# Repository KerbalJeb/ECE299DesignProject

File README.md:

# ECE299DesignProject

An Arduino Uno power alarm clock, complated as part of ECE299 at UVic.

The PCB desing files can be viewed online at:[CADLAB.io](https://cadlab.io/project/23071).

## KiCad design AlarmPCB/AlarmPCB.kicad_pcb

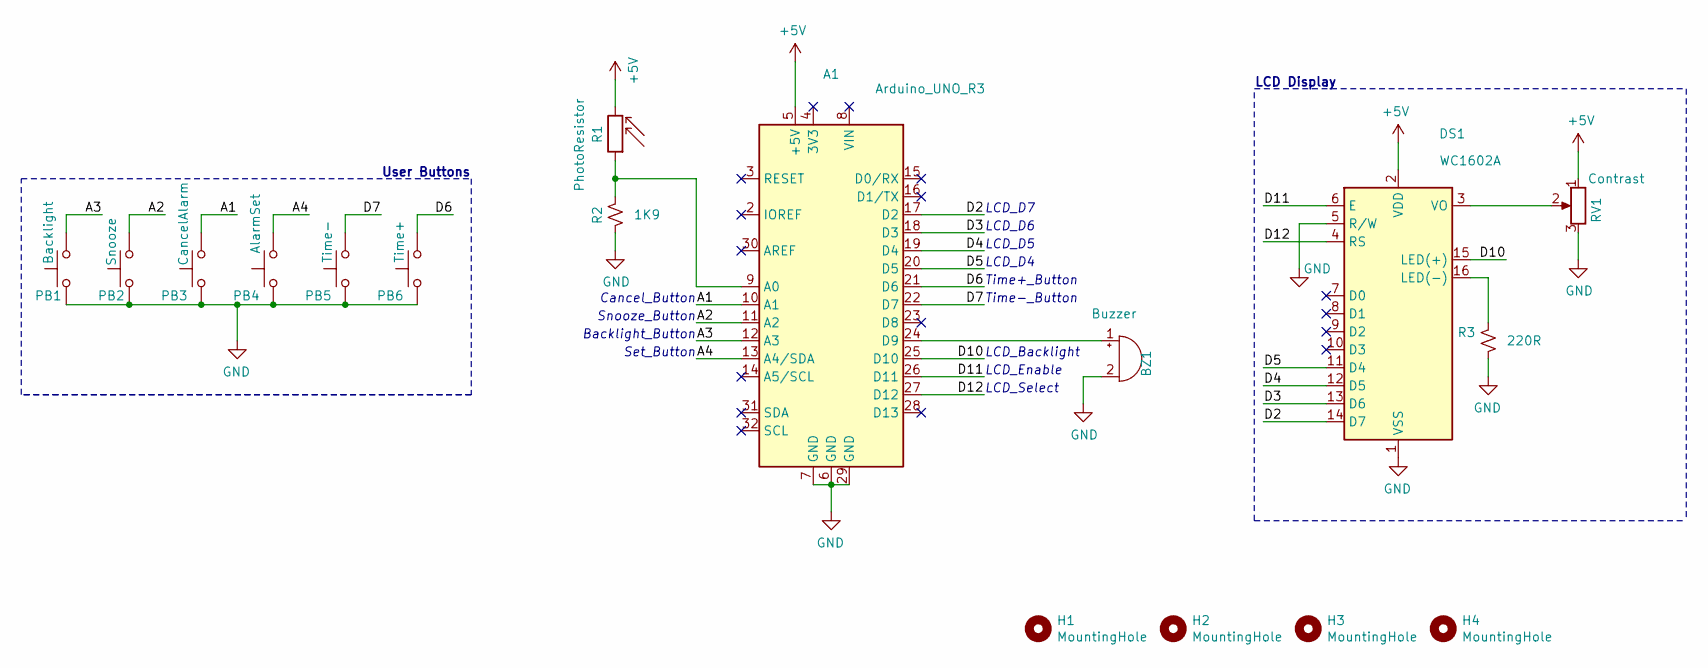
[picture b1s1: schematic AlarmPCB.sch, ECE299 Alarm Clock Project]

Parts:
A1: Arduino_UNO_R3
BZ1: Buzzer; Buzzer_D14mm_H7mm_P10mm
DS1: WC1602A
H1, H2, H3, H4: MountingHole; MountingHole_3.2mm_M3
PB1: Backlight; SW_TH_Tactile_Omron_B3F-10xx
PB2: Snooze; PinHeader_1x02_P2.54mm_Vertical
PB3: CancelAlarm; PinHeader_1x02_P2.54mm_Vertical
PB4: AlarmSet; SW_TH_Tactile_Omron_B3F-10xx
PB5: Time-; SW_TH_Tactile_Omron_B3F-10xx
PB6: Time+; SW_TH_Tactile_Omron_B3F-10xx
R1: PhotoResistor; PinHeader_1x02_P2.54mm_Vertical
R2: 1K9; R_Axial_DIN0309_L9.0mm_D3.2mm_P12.70mm_Horizontal
R3: 220R; R_Axial_DIN0309_L9.0mm_D3.2mm_P12.70mm_Horizontal
RV1: Contrast; Potentiometer_P120PK-Y25BR10K

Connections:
+5V: A1.5 (+5V), DS1.2 (VDD), R1.2, RV1.1
/A1: A1.10 (A1), PB3.1
/A2: A1.11 (A2), PB2.1
/A3: A1.12 (A3), PB1.1
/A4: A1.13 (A4/SDA), PB4.1
/D2: A1.17 (D2), DS1.14 (D7)
/D3: A1.18 (D3), DS1.13 (D6)
/D4: A1.19 (D4), DS1.12 (D5)
/D5: A1.20 (D5), DS1.11 (D4)
/D6: A1.21 (D6), PB6.1
/D7: A1.22 (D7), PB5.1
/D10: A1.25 (D10), DS1.15 (LED(+))
/D11: A1.26 (D11), DS1.6 (E)
/D12: A1.27 (D12), DS1.4 (RS)
GND: A1.6 (GND), A1.7 (GND), A1.29 (GND), BZ1.2 (+), DS1.1 (VSS), DS1.5 (R/W), PB1.2, PB2.2, PB3.2, PB4.2, PB5.2, PB6.2, R2.1, R3.2, RV1.3
unnamed: A1.9 (A0), R1.1, R2.2
unnamed: A1.24 (D9), BZ1.1 (-)
unnamed: DS1.3 (VO), RV1.2
unnamed: DS1.16 (LED(-)), R3.1

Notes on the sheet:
LCD Display
User Buttons
LCD_Enable
LCD_Select
LCD_D7
LCD_D6
LCD_D5
LCD_D4
LCD_Backlight
Time+_Button
Time-_Button
Cancel_Button
Snooze_Button
Backlight_Button
Set_Button

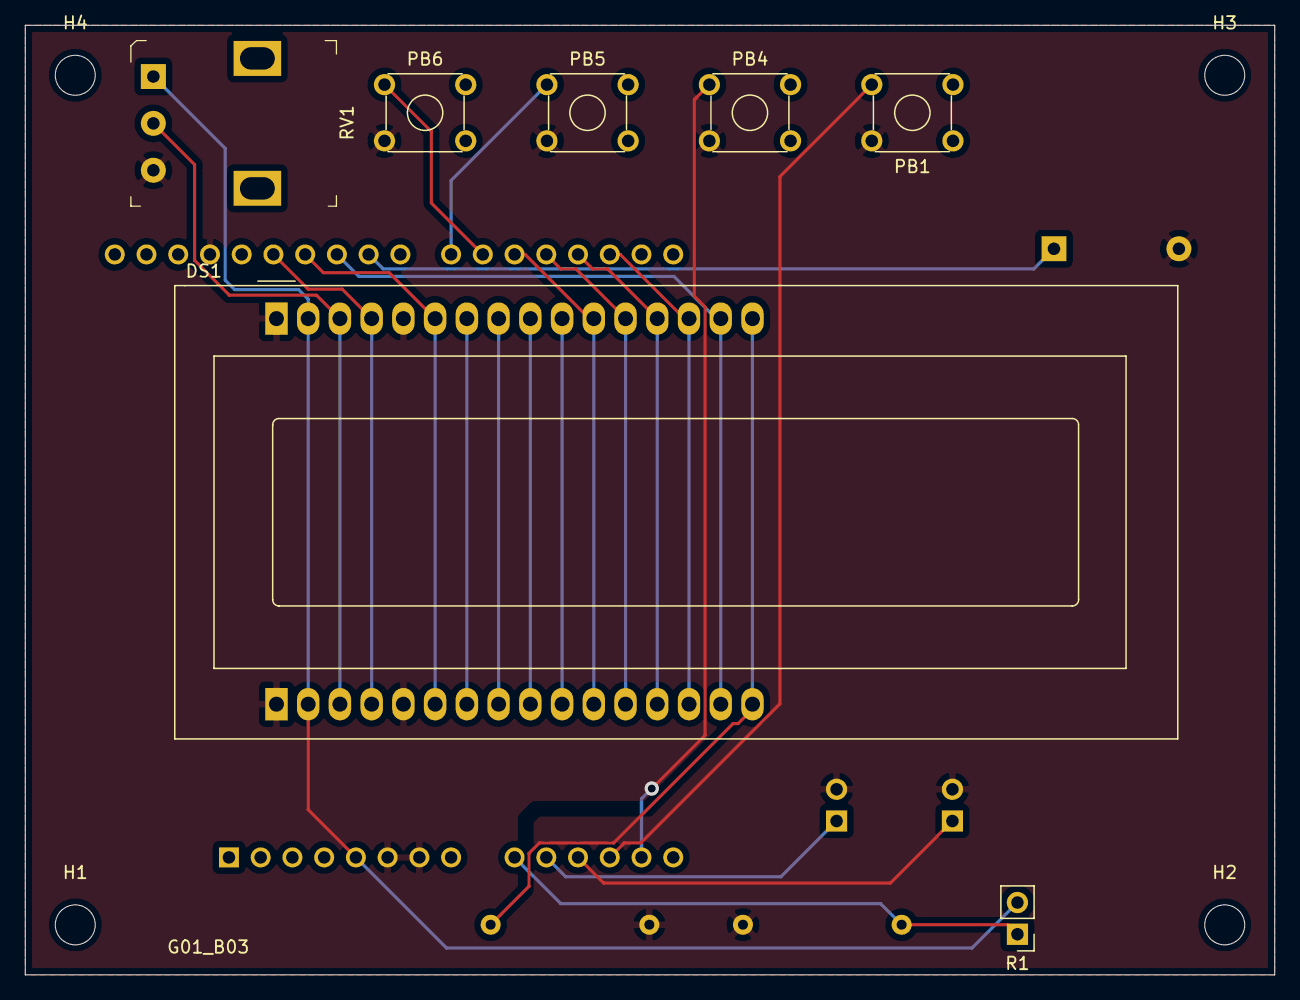
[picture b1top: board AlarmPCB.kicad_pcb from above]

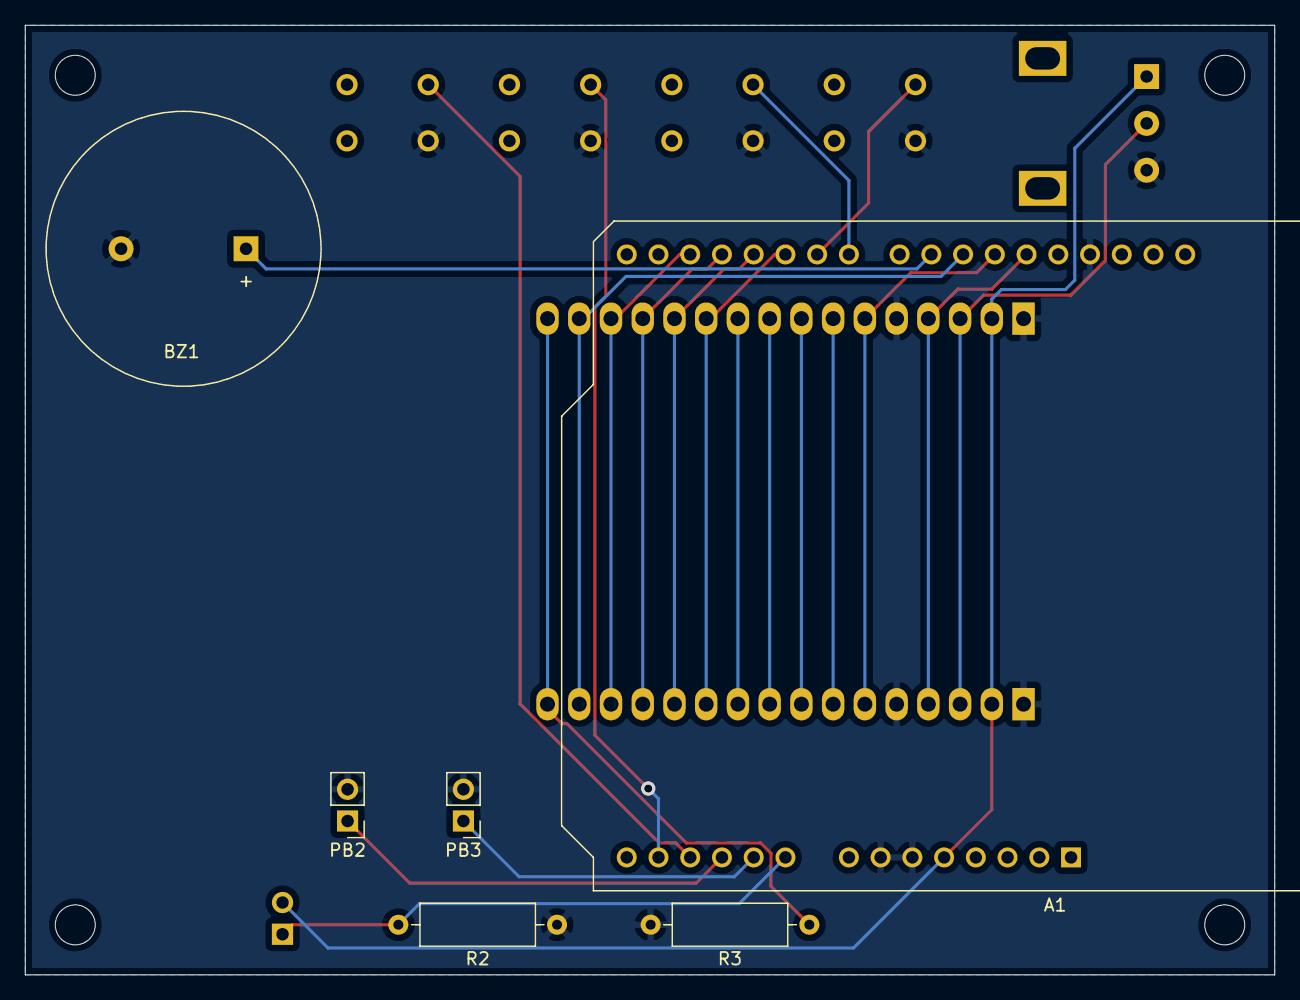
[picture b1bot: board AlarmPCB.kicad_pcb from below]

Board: 2 copper layers, 100.0 x 76.0 mm, 17 parts (6 on the bottom side), 19 nets.

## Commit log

2020-07-03 Backlink to CADLAB.io has been added.
2020-07-03 Added Arduino and display to schematic
2020-07-04 Added Latex and Travis File
2020-07-04 Updated Travis FIle to Deploy pdf on commit
2020-07-04 Complining Arduino Code on commit
2020-07-04 Removed GUI Code from travis.yml
2020-07-04 Removed Install boards line
2020-07-04 Making sure build fails correctly
2020-07-04 Fixed Build
2020-07-08 Addded LCD
2020-07-08 Added test
2020-07-08 Added initial circuit layout
2020-07-09 Changed look of sch
2020-07-11 Cleaned up layout of sch
2020-07-14 Upated Report Template
2020-07-14 Added basic clock logic
2020-07-14 Fixed formatting
2020-07-15 Rough Draft
2020-07-15 Fixed push-button numbering
2020-07-16 Added UI and Time Setting Logic
2020-07-16 Removed Redudant States
2020-07-16 Added Alarm Setting Logic
2020-07-16 Commented most of code with doxygen style comments
2020-07-16 Updated TODOs
2020-07-16 Added vscode config files
2020-07-18 Improved time set UI
2020-07-19 Made PCB
2020-07-19 Updated arduino config
2020-07-22 Updated Comments
2020-07-24 Updated PCB GND Layer
2020-07-24 Fixed Layout Issues
2020-07-24 Moved pot
2020-07-25 Added more hole to track clerance
2020-07-25 PCB Dimensions
2020-07-25 Minor adjustments
2020-07-25 Moved buttons
2020-07-25 Fixed LCD Dims
2020-07-25 Repoured GND Plane
2020-07-26 Moved Arduino to fix clearance issues
2020-07-26 Rewired LCD
2020-07-26 PCB revisions
2020-07-26 Added gerbers to gitignore
2020-07-26 Updated Footprints
2020-07-26 Revert "Updated Footprints"
    This reverts commit dd3b0c72e674ffb159cfd3c8d42ceca2805da80f.
2020-07-26 Updated Pot footprint
2020-07-26 PCB rev
2020-07-27 Final PCB
2020-07-28 Added auto backlight adjustment
2020-07-28 Corrected last commit
2020-07-28 Removed sprintf due to stupid tinkercad
2020-07-28 Added backlight UI
2020-07-28 Added alarm and snooze
2020-07-28 Fixed snooze display bug
2020-07-29 Fixed display problem when leaving back-light menu
2020-08-14 Added Test FIle
2020-08-18 Updated Resistor Values
2020-08-18 reformatted Code for report
2020-08-18 Fixed Short
2020-08-18 Moved test code to fix build
2020-08-26 Fixed some UI buttons not working after alarm trigger
2020-08-27 Added Report Files
